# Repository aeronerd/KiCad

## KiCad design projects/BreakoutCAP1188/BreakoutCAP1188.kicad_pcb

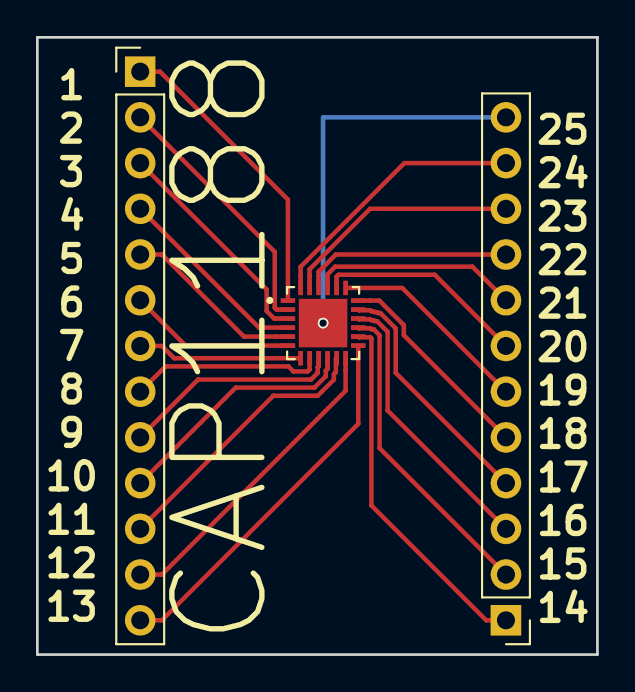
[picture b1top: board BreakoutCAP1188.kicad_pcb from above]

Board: 2 copper layers, 31.1 x 34.3 mm, 3 parts (0 on the bottom side), 25 nets.

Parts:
J1: Conn_01x13; Pin_Header_Straight_1x13_Pitch2.54mm
J2: Conn_01x12; Pin_Header_Straight_1x12_Pitch2.54mm
U1: CAP1188; QFN50P400X400X90-25N

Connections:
unnamed: J1.1, U1.1
unnamed: J1.2, U1.2
unnamed: J1.3, U1.3
unnamed: J1.4, U1.4
unnamed: J1.5, U1.5
unnamed: J1.6, U1.6
unnamed: J1.7, U1.7
unnamed: J1.8, U1.8
unnamed: J1.9, U1.9
unnamed: J1.10, U1.10
unnamed: J1.11, U1.11
unnamed: J1.12, U1.12
unnamed: J1.13, U1.13
unnamed: J2.1, U1.14
unnamed: J2.2, U1.15
unnamed: J2.3, U1.16
unnamed: J2.4, U1.17
unnamed: J2.5, U1.18
unnamed: J2.6, U1.19
unnamed: J2.7, U1.20
unnamed: J2.8, U1.21
unnamed: J2.9, U1.22
unnamed: J2.10, U1.23
unnamed: J2.11, U1.24
unnamed: J2.12, U1.25

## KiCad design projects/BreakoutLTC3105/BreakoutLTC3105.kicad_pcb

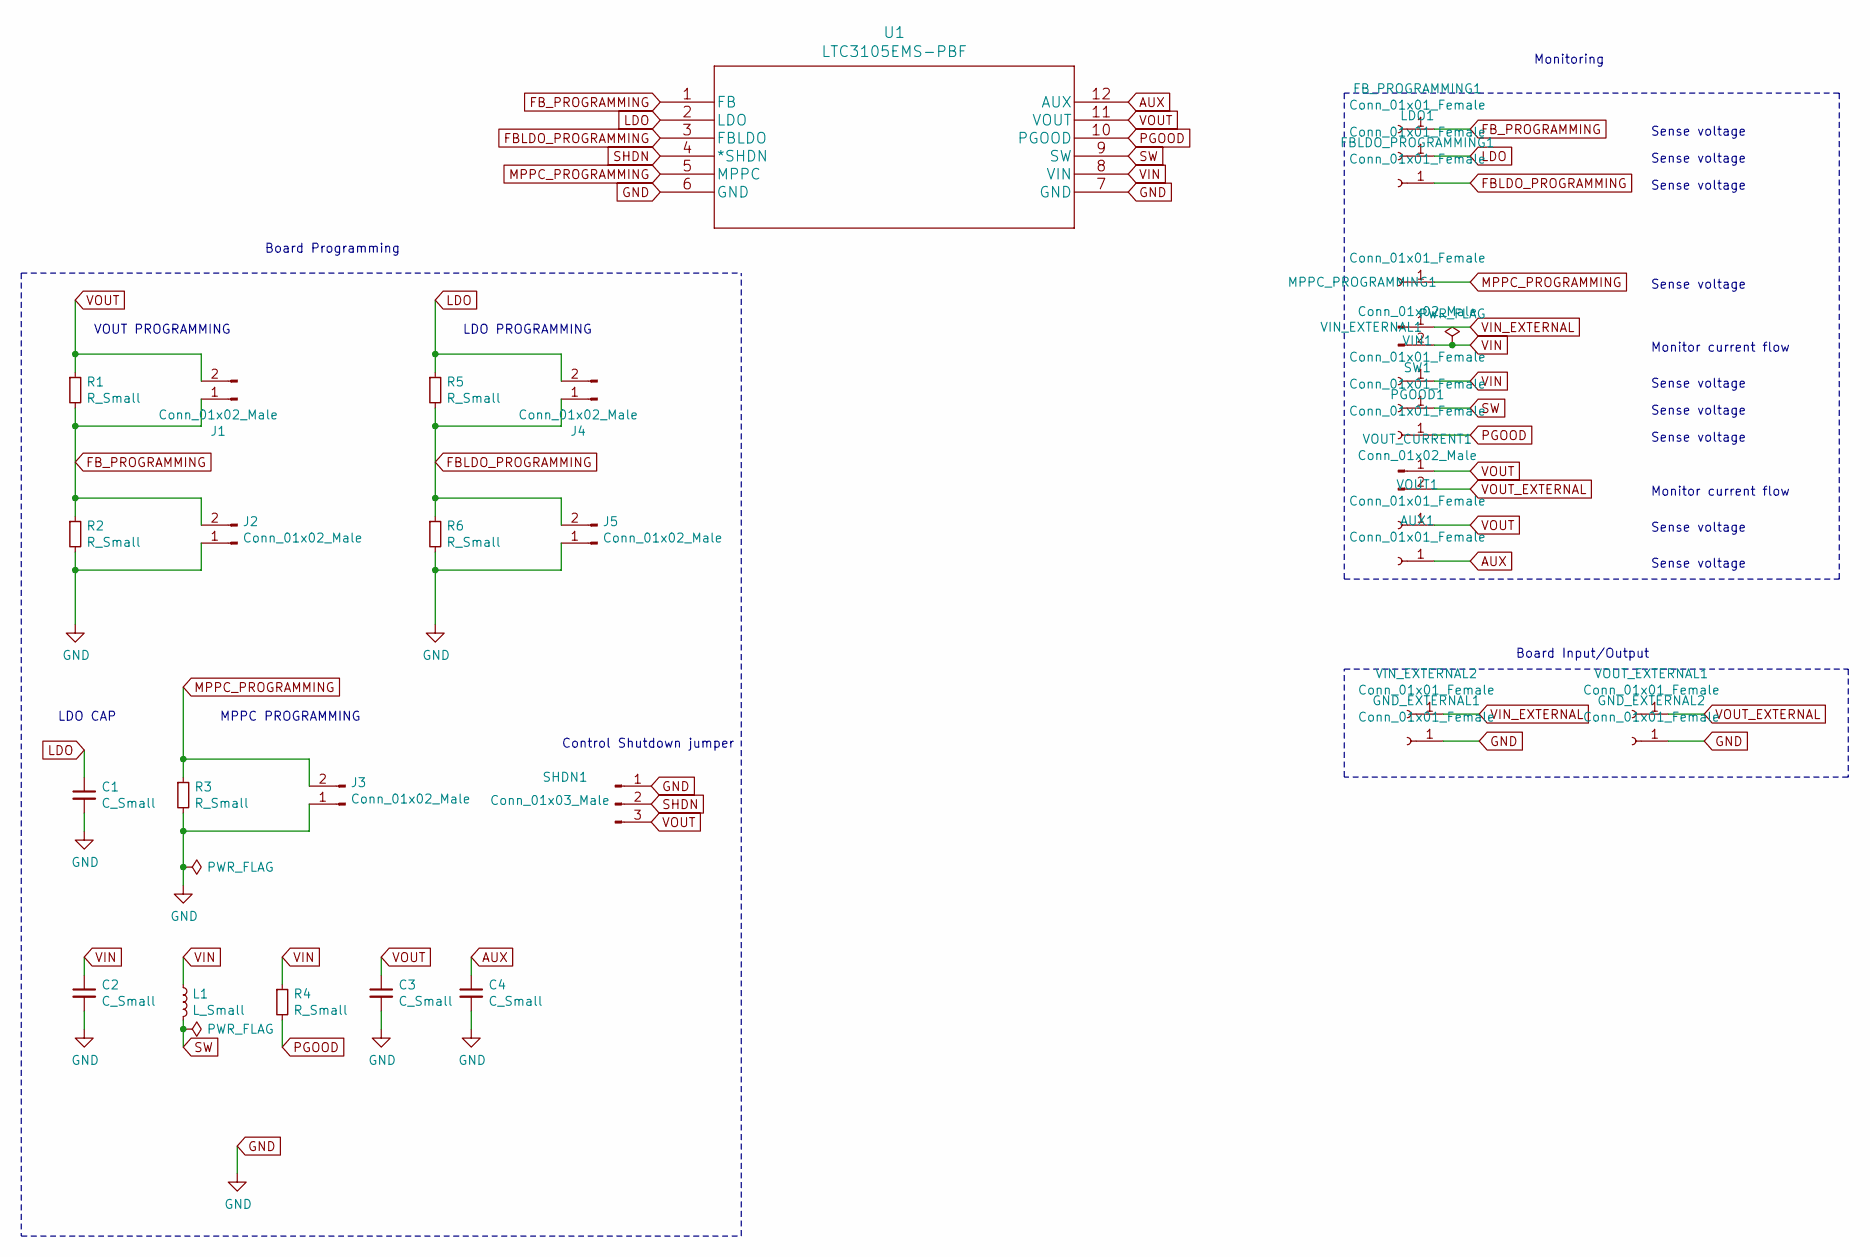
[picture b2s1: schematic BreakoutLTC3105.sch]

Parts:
AUX1: Conn_01x01_Female; Socket_Strip_Straight_1x01_Pitch2.54mm
C1, C2, C3, C4: C_Small; C_0603_HandSoldering
FBLDO_PROGRAMMING1: Conn_01x01_Female; Socket_Strip_Straight_1x01_Pitch2.54mm
FB_PROGRAMMING1: Conn_01x01_Female; Socket_Strip_Straight_1x01_Pitch2.54mm
GND_EXTERNAL1, GND_EXTERNAL2: Conn_01x01_Female; Socket_Strip_Straight_1x01_Pitch2.54mm
J1, J2, J3, J4, J5: Conn_01x02_Male; Pin_Header_Straight_1x02_Pitch2.54mm
L1: L_Small; coilcraft-MSS5131-103
LDO1: Conn_01x01_Female; Socket_Strip_Straight_1x01_Pitch2.54mm
MPPC_PROGRAMMING1: Conn_01x01_Female; Socket_Strip_Straight_1x01_Pitch2.54mm
PGOOD1: Conn_01x01_Female; Socket_Strip_Straight_1x01_Pitch2.54mm
R1, R2, R3, R4, R5, R6: R_Small; R_0603_HandSoldering
SHDN1: Conn_01x03_Male; Pin_Header_Straight_1x03_Pitch2.54mm
SW1: Conn_01x01_Female; Socket_Strip_Straight_1x01_Pitch2.54mm
U1: LTC3105EMS-PBF
VIN1: Conn_01x01_Female; Socket_Strip_Straight_1x01_Pitch2.54mm
VIN_EXTERNAL1: Conn_01x02_Male; Pin_Header_Straight_1x02_Pitch2.54mm
VIN_EXTERNAL2: Conn_01x01_Female; Socket_Strip_Straight_1x01_Pitch2.54mm
VOUT1: Conn_01x01_Female; Socket_Strip_Straight_1x01_Pitch2.54mm
VOUT_CURRENT1: Conn_01x02_Male; Pin_Header_Straight_1x02_Pitch2.54mm
VOUT_EXTERNAL1: Conn_01x01_Female; Socket_Strip_Straight_1x01_Pitch2.54mm

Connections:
AUX: AUX1.1, C4.1, U1.12 (AUX)
FBLDO_PROGRAMMING: FBLDO_PROGRAMMING1.1, J4.1, J5.2, R5.2, R6.1, U1.3 (FBLDO)
FB_PROGRAMMING: FB_PROGRAMMING1.1, J1.1, J2.2, R1.2, R2.1, U1.1 (FB)
GND: C1.2, C2.2, C3.2, C4.2, GND_EXTERNAL1.1, GND_EXTERNAL2.1, J2.1, J3.1, J5.1, R2.2, R3.2, R6.2, SHDN1.1, U1.6 (GND), U1.7 (GND)
LDO: C1.1, J4.2, LDO1.1, R5.1, U1.2 (LDO)
MPPC_PROGRAMMING: J3.2, MPPC_PROGRAMMING1.1, R3.1, U1.5 (MPPC)
PGOOD: PGOOD1.1, R4.2, U1.10 (PGOOD)
SHDN: SHDN1.2, U1.4 (*SHDN)
SW: L1.2, SW1.1, U1.9 (SW)
VIN: C2.1, L1.1, R4.1, U1.8 (VIN), VIN1.1, VIN_EXTERNAL1.2
VIN_EXTERNAL: VIN_EXTERNAL1.1, VIN_EXTERNAL2.1
VOUT: C3.1, J1.2, R1.1, SHDN1.3, U1.11 (VOUT), VOUT1.1, VOUT_CURRENT1.1
VOUT_EXTERNAL: VOUT_CURRENT1.2, VOUT_EXTERNAL1.1

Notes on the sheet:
VOUT PROGRAMMING
LDO CAP
LDO PROGRAMMING
Monitor current flow
Sense voltage
Monitoring
Control Shutdown jumper
Board Input/Output
Board Programming
MPPC PROGRAMMING

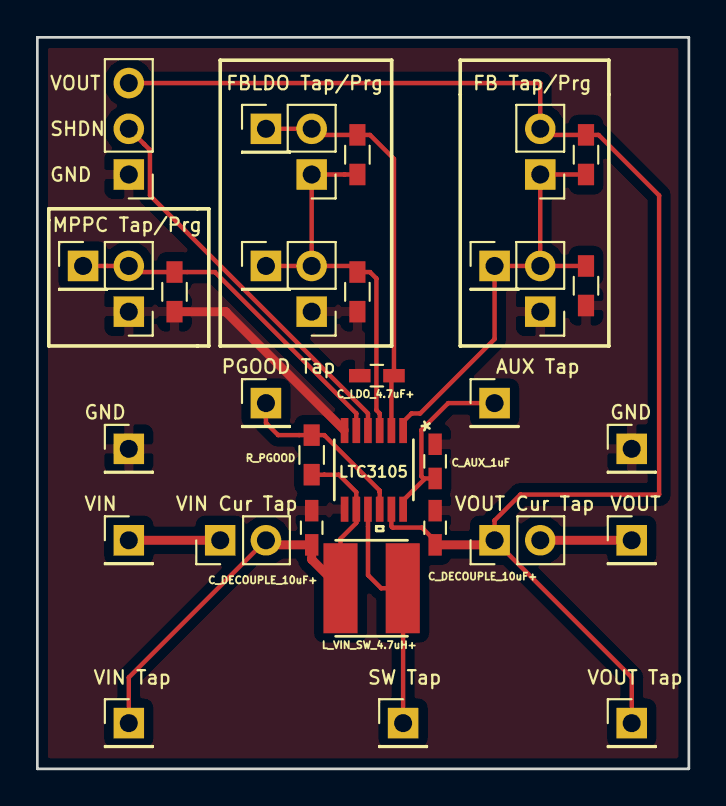
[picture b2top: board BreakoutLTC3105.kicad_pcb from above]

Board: 2 copper layers, 36.2 x 40.6 mm, 33 parts (0 on the bottom side), 13 nets.

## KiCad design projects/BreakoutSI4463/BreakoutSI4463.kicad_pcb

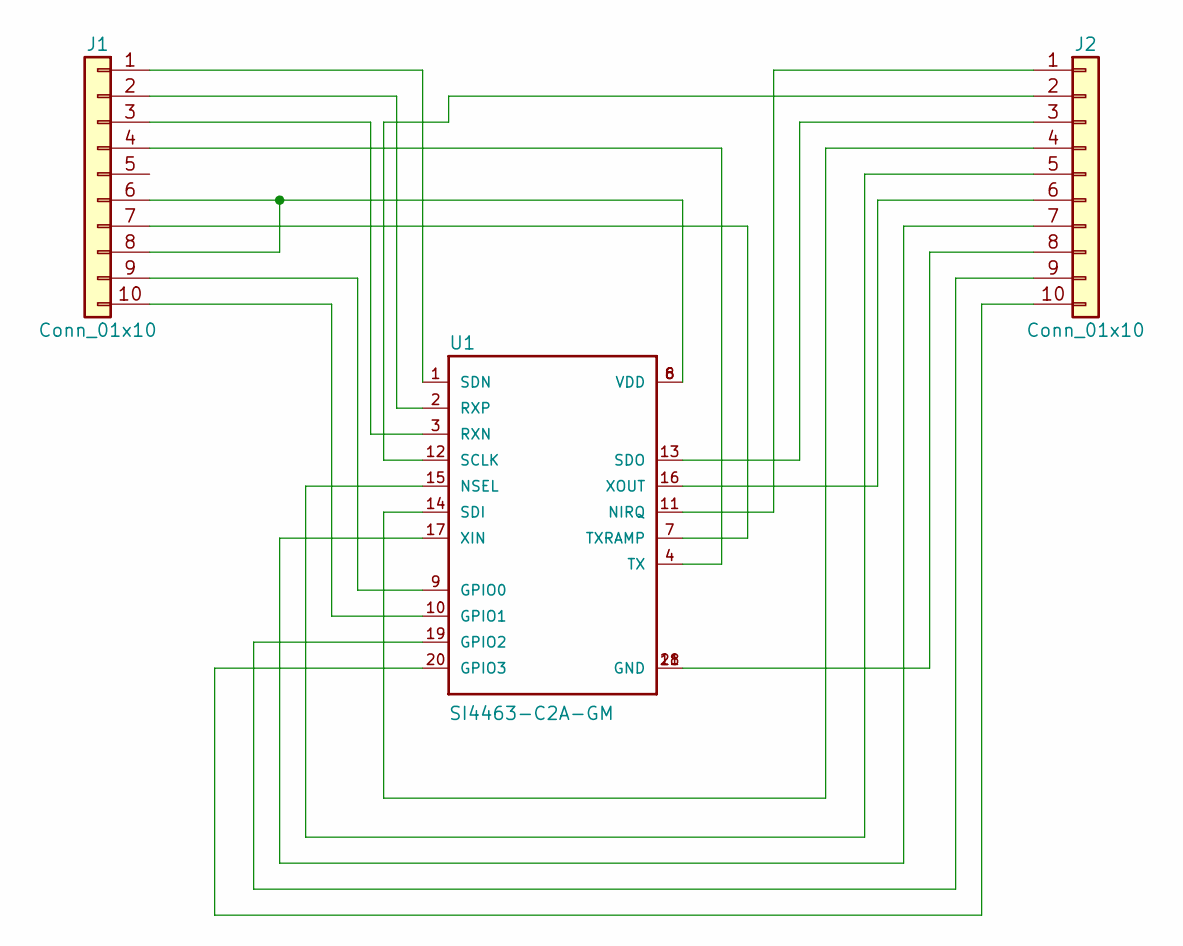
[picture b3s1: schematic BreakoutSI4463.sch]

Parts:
J1, J2: Conn_01x10; Pin_Header_Straight_1x10_Pitch2.54mm
U1: SI4463-C2A-GM; QFN50P400X400X90-20N

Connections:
unnamed: J1.1, U1.1 (SDN)
unnamed: J1.2, U1.2 (RXP)
unnamed: J1.3, U1.3 (RXN)
unnamed: J1.4, U1.4 (TX)
unnamed: J1.6, J1.8, U1.6 (VDD), U1.8 (VDD)
unnamed: J1.7, U1.7 (TXRAMP)
unnamed: J1.9, U1.9 (GPIO0)
unnamed: J1.10, U1.10 (GPIO1)
unnamed: J2.1, U1.11 (NIRQ)
unnamed: J2.2, U1.12 (SCLK)
unnamed: J2.3, U1.13 (SDO)
unnamed: J2.4, U1.14 (SDI)
unnamed: J2.5, U1.15 (NSEL)
unnamed: J2.6, U1.16 (XOUT)
unnamed: J2.7, U1.17 (XIN)
unnamed: J2.8, U1.18 (GND), U1.21 (GND)
unnamed: J2.9, U1.19 (GPIO2)
unnamed: J2.10, U1.20 (GPIO3)

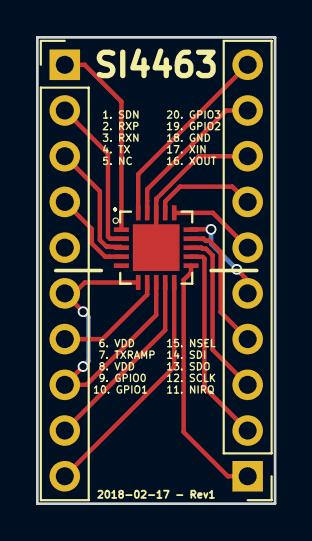
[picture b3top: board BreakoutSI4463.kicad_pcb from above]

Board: 2 copper layers, 13.2 x 25.9 mm, 3 parts (0 on the bottom side), 18 nets.

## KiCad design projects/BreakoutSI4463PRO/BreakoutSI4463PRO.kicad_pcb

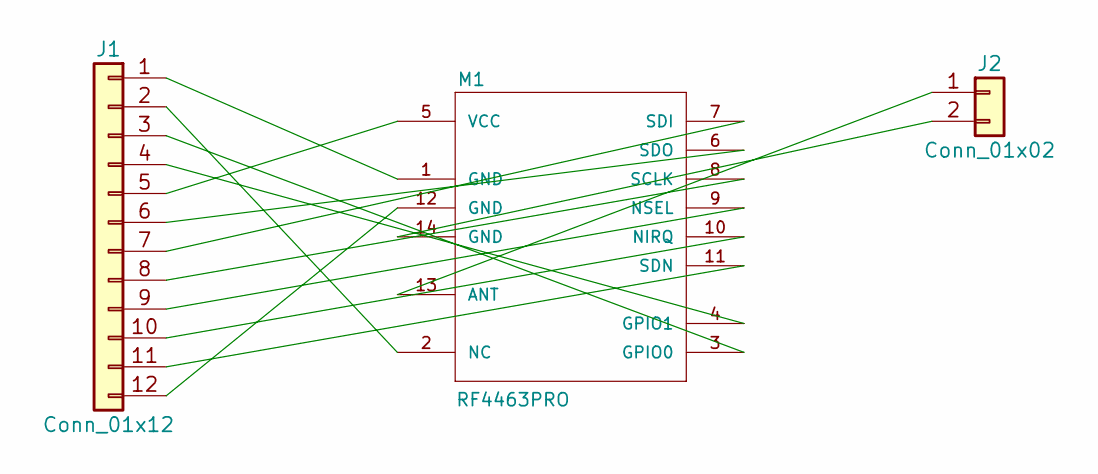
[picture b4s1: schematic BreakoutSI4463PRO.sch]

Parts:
J1: Conn_01x12; Pin_Header_Straight_1x12_Pitch2.54mm
J2: Conn_01x02; Pin_Header_Straight_1x02_Pitch2.54mm
M1: RF4463PRO; RF4436PRO-STD_BOARD

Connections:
unnamed: J1.1, M1.1 (GND)
unnamed: J1.2, M1.2 (NC)
unnamed: J1.3, M1.3 (GPIO0)
unnamed: J1.4, M1.4 (GPIO1)
unnamed: J1.5, M1.5 (VCC)
unnamed: J1.6, M1.6 (SDO)
unnamed: J1.7, M1.7 (SDI)
unnamed: J1.8, M1.8 (SCLK)
unnamed: J1.9, M1.9 (NSEL)
unnamed: J1.10, M1.10 (NIRQ)
unnamed: J1.11, M1.11 (SDN)
unnamed: J1.12, M1.12 (GND)
unnamed: J2.1, M1.13 (ANT)
unnamed: J2.2, M1.14 (GND)

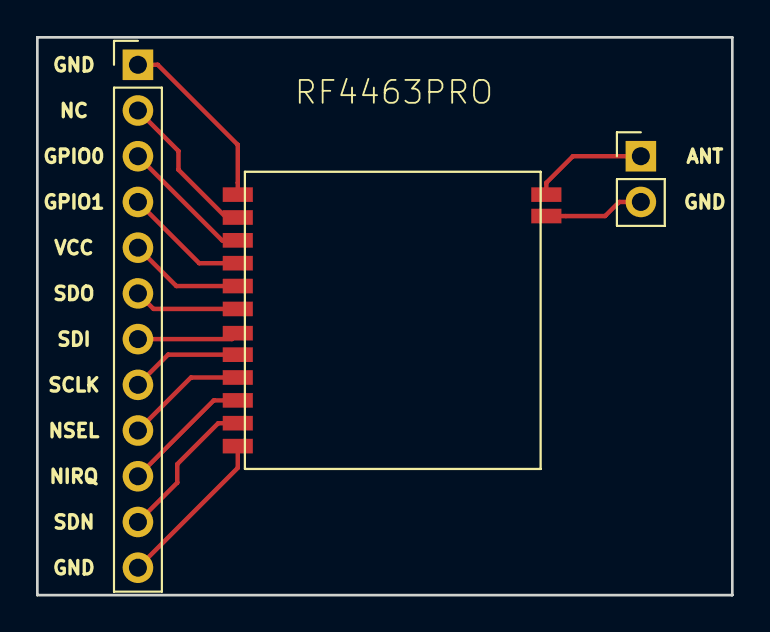
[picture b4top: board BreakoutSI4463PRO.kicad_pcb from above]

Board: 2 copper layers, 38.6 x 31.0 mm, 3 parts (0 on the bottom side), 14 nets.

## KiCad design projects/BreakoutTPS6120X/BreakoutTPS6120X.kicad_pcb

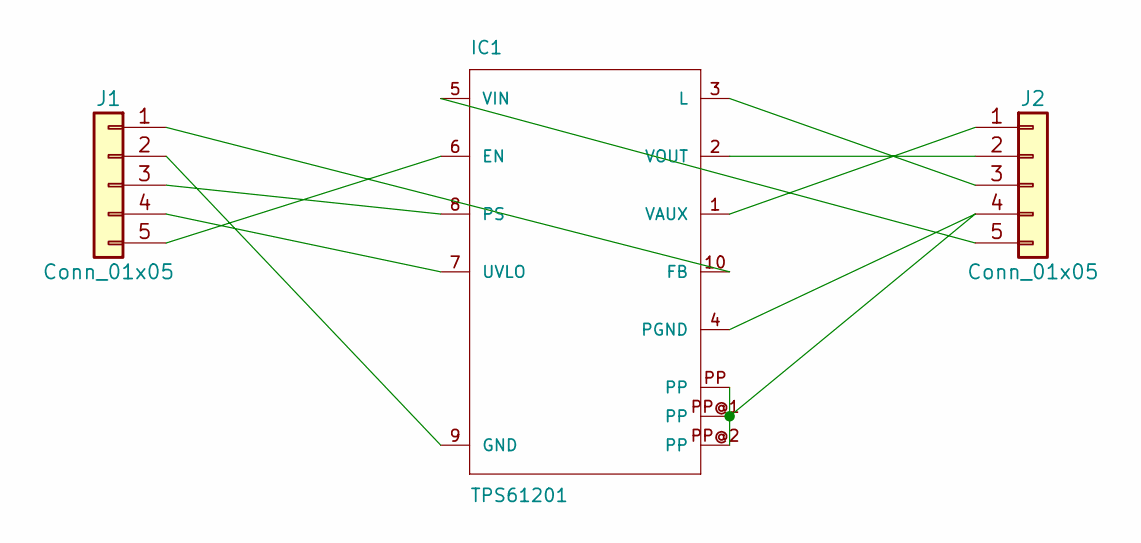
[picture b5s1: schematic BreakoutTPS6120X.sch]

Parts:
IC1: TPS61201; texas-S-PDSO-N10
J1, J2: Conn_01x05; Pin_Header_Straight_1x05_Pitch2.54mm

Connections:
unnamed: IC1.1 (VAUX), J2.1
unnamed: IC1.2 (VOUT), J2.2
unnamed: IC1.3 (L), J2.3
unnamed: IC1.4 (PGND), IC1.PP, IC1.PP@1 (PP), IC1.PP@2 (PP), J2.4
unnamed: IC1.5 (VIN), J2.5
unnamed: IC1.6 (EN), J1.5
unnamed: IC1.7 (UVLO), J1.4
unnamed: IC1.8 (PS), J1.3
unnamed: IC1.9 (GND), J1.2
unnamed: IC1.10 (FB), J1.1

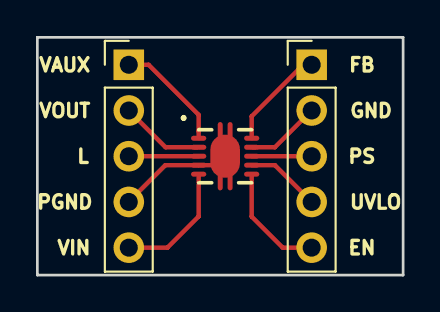
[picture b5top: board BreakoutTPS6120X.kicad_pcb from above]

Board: 2 copper layers, 20.3 x 13.2 mm, 3 parts (0 on the bottom side), 10 nets.

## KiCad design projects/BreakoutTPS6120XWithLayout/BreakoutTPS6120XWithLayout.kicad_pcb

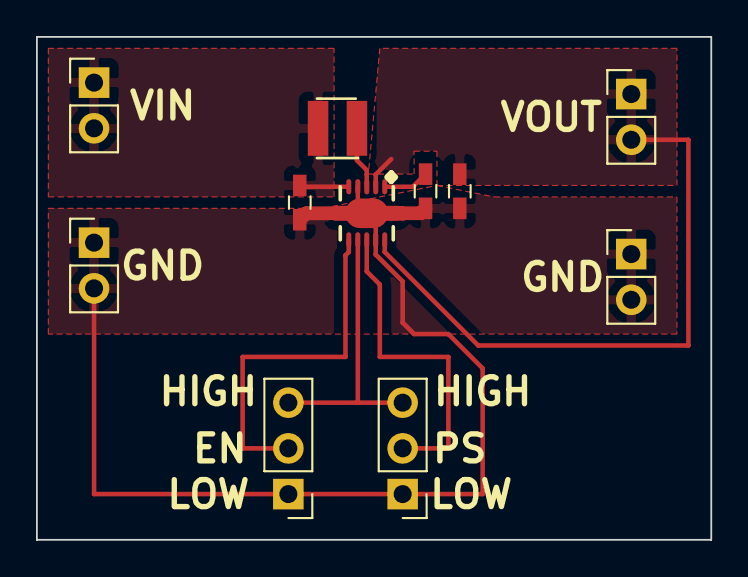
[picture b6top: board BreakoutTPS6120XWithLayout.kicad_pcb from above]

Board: 2 copper layers, 37.5 x 27.9 mm, 11 parts (0 on the bottom side), 7 nets.

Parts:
C1, C2, C3: 10uF; C_0603_HandSoldering
J1, J2, J3, J4: Conn_01x02; Pin_Header_Straight_1x02_Pitch2.54mm
J5, J6: Conn_01x03; Pin_Header_Straight_1x03_Pitch2.54mm
L1: 2.2uH; coilcraft-LPS3015-222
REG_3V3_BOARD1: TPS61201; texas-S-PDSO-N10

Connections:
EN: J5.2, REG_3V3_BOARD1.6
GND: C1.2, C2.2, C3.2, J1.1, J1.2, J4.1, J4.2, J5.1, J6.1, REG_3V3_BOARD1.4, REG_3V3_BOARD1.9, REG_3V3_BOARD1.PP, REG_3V3_BOARD1.PP@1, REG_3V3_BOARD1.PP@2
L: L1.2, REG_3V3_BOARD1.3
PS: J6.2, REG_3V3_BOARD1.8
VAUX: C2.1, REG_3V3_BOARD1.1
VIN: C1.1, J2.1, J2.2, J5.3, J6.3, L1.1, REG_3V3_BOARD1.5, REG_3V3_BOARD1.7
VOUT: C3.1, J3.1, J3.2, REG_3V3_BOARD1.2, REG_3V3_BOARD1.10

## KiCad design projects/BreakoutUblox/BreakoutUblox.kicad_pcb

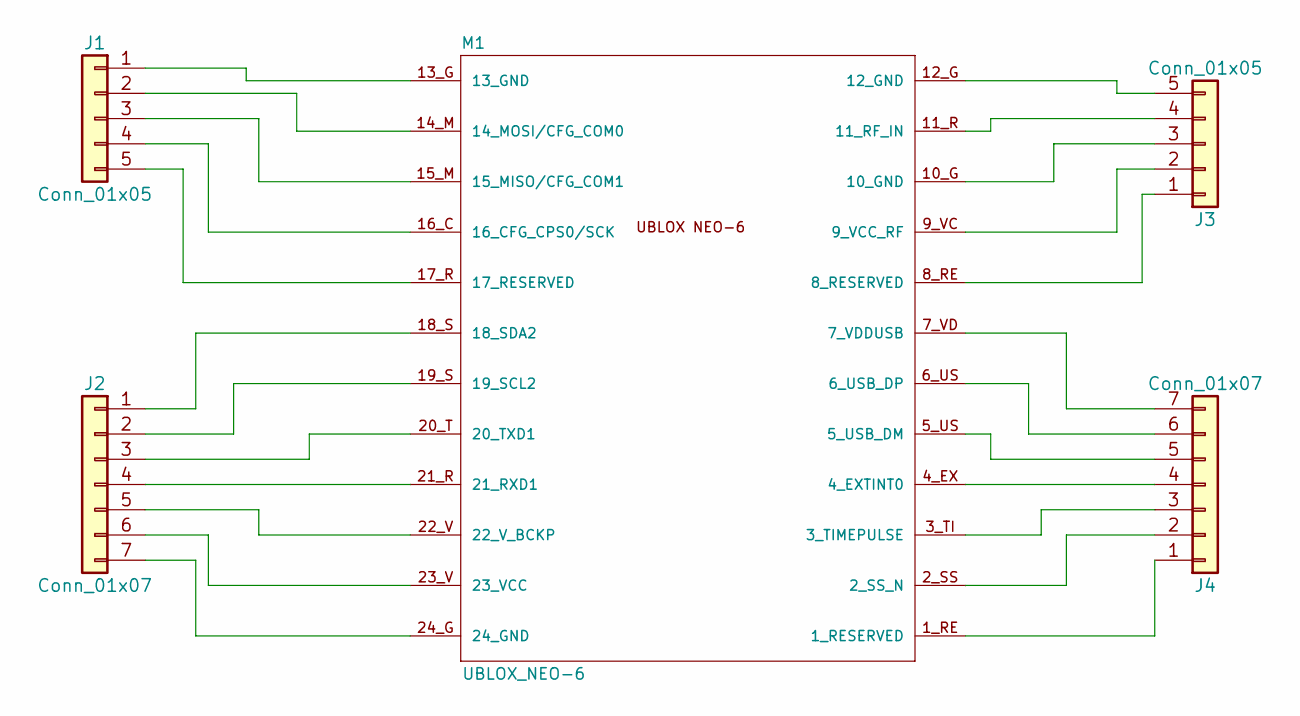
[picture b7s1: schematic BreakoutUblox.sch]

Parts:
J1, J3: Conn_01x05; Pin_Header_Straight_1x05_Pitch2.54mm
J2, J4: Conn_01x07; Pin_Header_Straight_1x07_Pitch2.54mm
M1: UBLOX_NEO-6

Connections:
unnamed: J1.1, M1.13_G (13_GND)
unnamed: J1.2, M1.14_M (14_MOSI/CFG_COM0)
unnamed: J1.3, M1.15_M (15_MISO/CFG_COM1)
unnamed: J1.4, M1.16_C (16_CFG_CPS0/SCK)
unnamed: J1.5, M1.17_R (17_RESERVED)
unnamed: J2.1, M1.18_S (18_SDA2)
unnamed: J2.2, M1.19_S (19_SCL2)
unnamed: J2.3, M1.20_T (20_TXD1)
unnamed: J2.4, M1.21_R (21_RXD1)
unnamed: J2.5, M1.22_V (22_V_BCKP)
unnamed: J2.6, M1.23_V (23_VCC)
unnamed: J2.7, M1.24_G (24_GND)
unnamed: J3.1, M1.8_RE (8_RESERVED)
unnamed: J3.2, M1.9_VC (9_VCC_RF)
unnamed: J3.3, M1.10_G (10_GND)
unnamed: J3.4, M1.11_R (11_RF_IN)
unnamed: J3.5, M1.12_G (12_GND)
unnamed: J4.1, M1.1_RE (1_RESERVED)
unnamed: J4.2, M1.2_SS (2_SS_N)
unnamed: J4.3, M1.3_TI (3_TIMEPULSE)
unnamed: J4.4, M1.4_EX (4_EXTINT0)
unnamed: J4.5, M1.5_US (5_USB_DM)
unnamed: J4.6, M1.6_US (6_USB_DP)
unnamed: J4.7, M1.7_VD (7_VDDUSB)

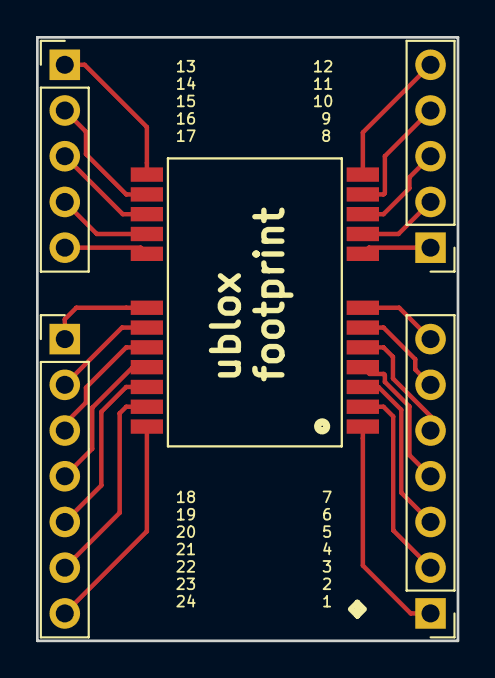
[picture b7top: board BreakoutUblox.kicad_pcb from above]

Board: 2 copper layers, 23.4 x 33.5 mm, 5 parts (0 on the bottom side), 24 nets.

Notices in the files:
parts and their libraries:
Copyright 2016 Accelerated Designs. All rights reserved.
